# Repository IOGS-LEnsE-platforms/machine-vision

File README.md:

# Machine Vision Platform
Documentation of the pedagogic platform about Machine Vision used during labwors @ LEnsE / IOGS / France

Watch the complete documentation [here !!!](https://iogs-lense.github.io/machine-vision/)

## About Institut d'Optique and LEnsE
The **LEnsE**, ***Laboratoire d'Enseignement Expérimental***, [Website](http://lense.institutoptique.fr/)

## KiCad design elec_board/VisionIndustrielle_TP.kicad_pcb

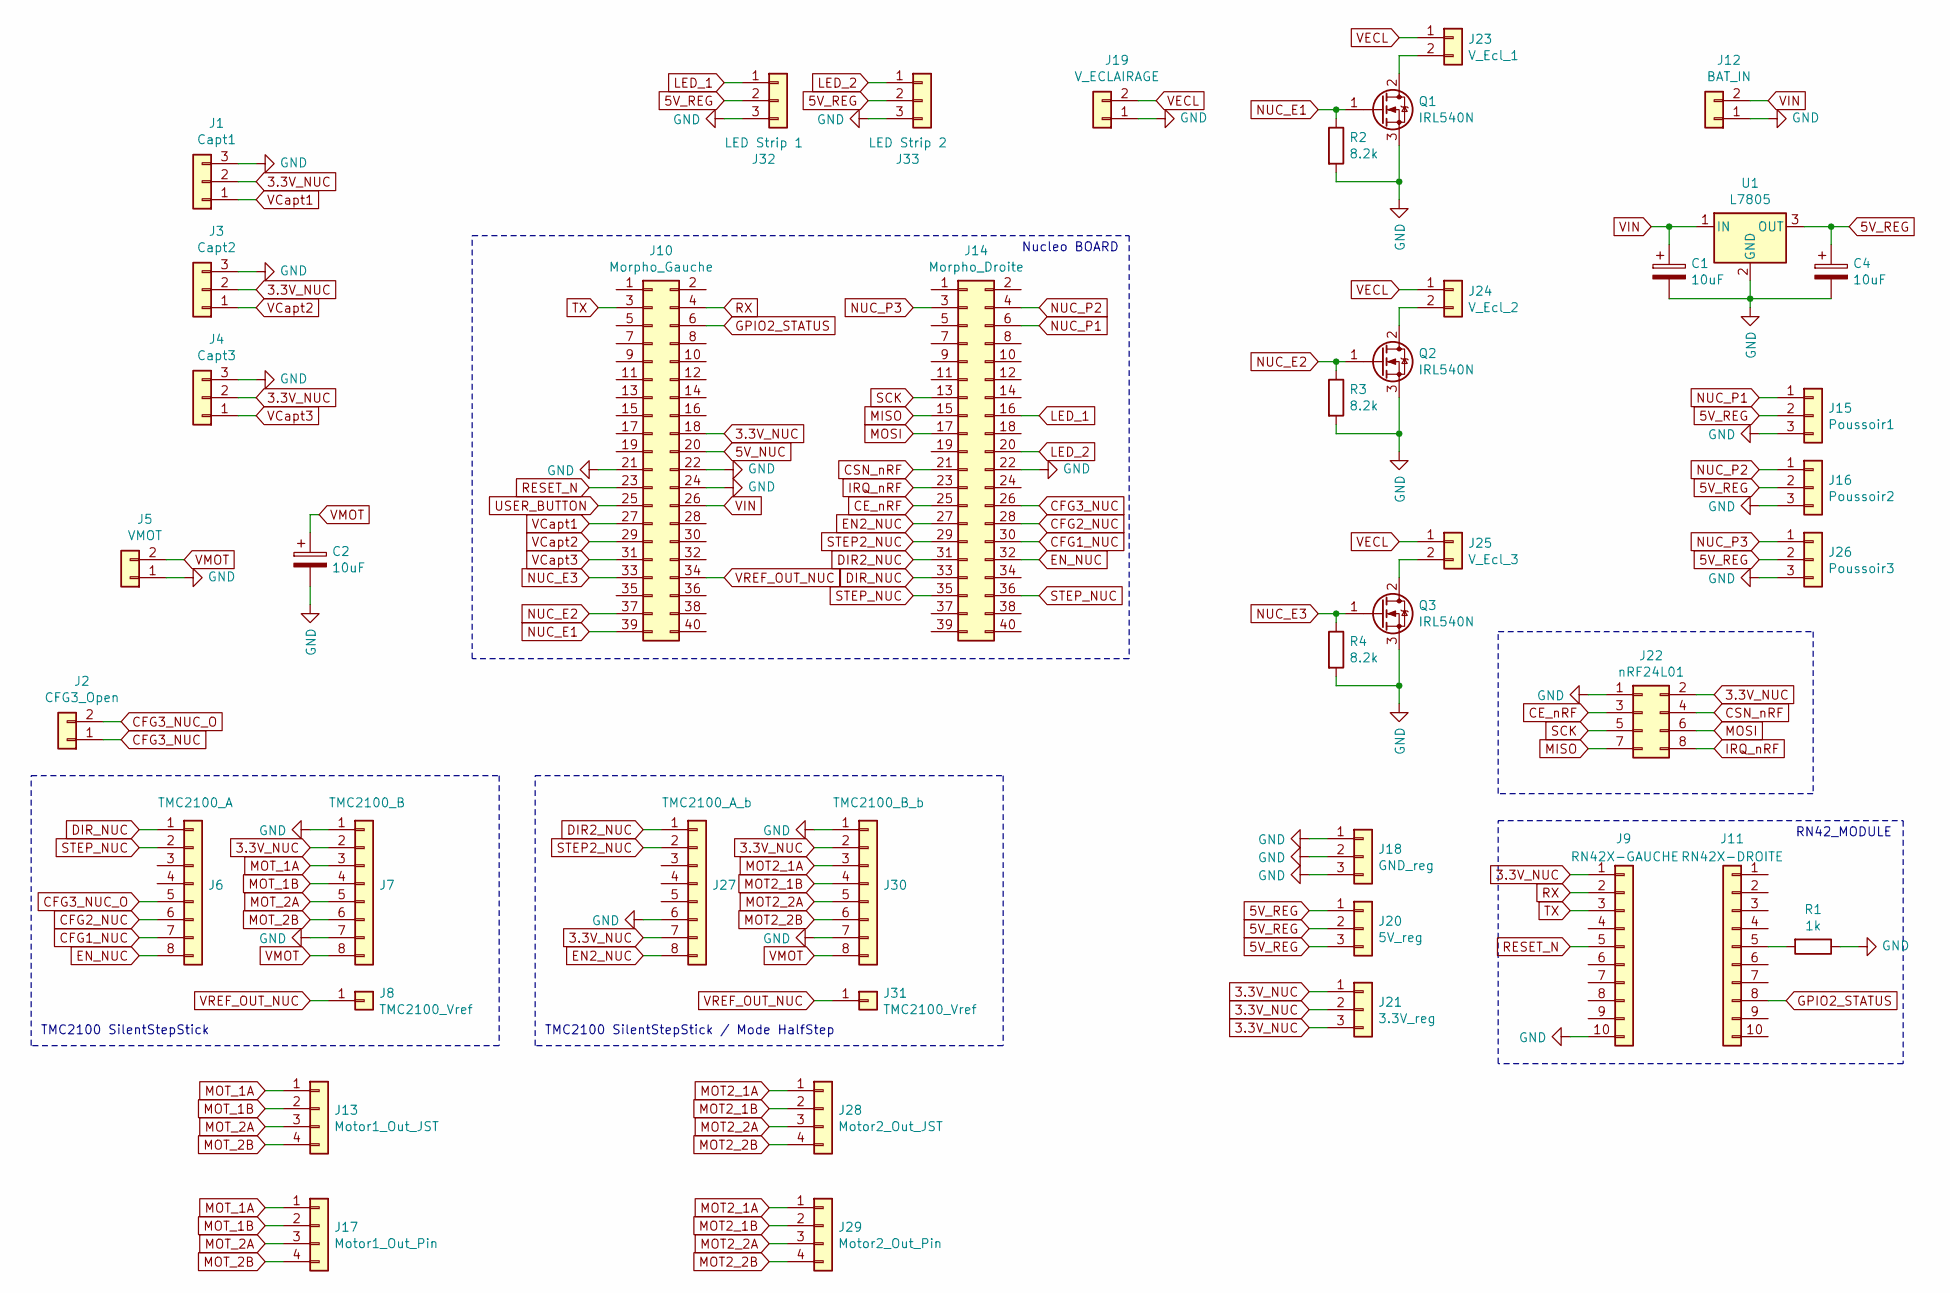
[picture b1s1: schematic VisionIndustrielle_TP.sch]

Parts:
C1, C2, C4: 10uF; CP_Radial_D10.0mm_P5.00mm
J1: Capt1; PinSocket_1x03_P2.54mm_Vertical
J2: CFG3_Open; PinSocket_1x02_P2.54mm_Vertical
J3: Capt2; PinSocket_1x03_P2.54mm_Vertical
J4: Capt3; PinSocket_1x03_P2.54mm_Vertical
J5: VMOT; TerminalBlock_Phoenix_MKDS-3-2-5.08_1x02_P5.08mm_Horizontal
J6: TMC2100_A; PinSocket_1x08_P2.54mm_Vertical
J7: TMC2100_B; PinSocket_1x08_P2.54mm_Vertical
J8, J31: TMC2100_Vref; PinSocket_1x01_P2.54mm_Vertical
J9: RN42X-GAUCHE; PinHeader_1x10_P2.00mm_Vertical
J10: Morpho_Gauche; PinHeader_2x20_P2.54mm_Vertical
J11: RN42X-DROITE; PinHeader_1x10_P2.00mm_Vertical
J12: BAT_IN; TerminalBlock_Phoenix_MKDS-3-2-5.08_1x02_P5.08mm_Horizontal
J13: Motor1_Out_JST; JST_PH_B4B-PH-K_1x04_P2.00mm_Vertical
J14: Morpho_Droite; PinHeader_2x20_P2.54mm_Vertical
J15: Poussoir1; PinHeader_1x03_P2.54mm_Horizontal
J16: Poussoir2; PinHeader_1x03_P2.54mm_Horizontal
J17: Motor1_Out_Pin; PinSocket_1x04_P2.54mm_Vertical
J18: GND_reg; PinHeader_1x03_P2.54mm_Vertical
J19: V_ECLAIRAGE; TerminalBlock_Phoenix_MKDS-3-2-5.08_1x02_P5.08mm_Horizontal
J20: 5V_reg; PinHeader_1x03_P2.54mm_Vertical
J21: 3.3V_reg; PinHeader_1x03_P2.54mm_Vertical
J22: nRF24L01; PinHeader_2x04_P2.54mm_Vertical
J23: V_Ecl_1; TerminalBlock_bornier-2_P5.08mm
J24: V_Ecl_2; TerminalBlock_bornier-2_P5.08mm
J25: V_Ecl_3; TerminalBlock_bornier-2_P5.08mm
J26: Poussoir3; PinHeader_1x03_P2.54mm_Horizontal
J27: TMC2100_A_b; PinSocket_1x08_P2.54mm_Vertical
J28: Motor2_Out_JST; JST_PH_B4B-PH-K_1x04_P2.00mm_Vertical
J29: Motor2_Out_Pin; PinSocket_1x04_P2.54mm_Vertical
J30: TMC2100_B_b; PinSocket_1x08_P2.54mm_Vertical
J32: LED Strip 1; PinSocket_1x03_P2.54mm_Vertical
J33: LED Strip 2; PinSocket_1x03_P2.54mm_Vertical
Q1, Q2, Q3: IRL540N; TO-220-3_Vertical
R1: 1k; R_Axial_DIN0207_L6.3mm_D2.5mm_P10.16mm_Horizontal
R2, R3, R4: 8.2k; R_Axial_DIN0207_L6.3mm_D2.5mm_P10.16mm_Horizontal
U1: L7805; TO-220-3_Horizontal_TabDown

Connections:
3.3V_NUC: J1.2, J3.2, J4.2, J7.2, J9.1, J10.18, J21.1, J21.2, J21.3, J22.2, J27.7, J30.2
5V_NUC: J10.20
5V_REG: C4.1, J15.2, J16.2, J20.1, J20.2, J20.3, J26.2, J32.2, J33.2, U1.3 (OUT)
CE_nRF: J14.25, J22.3
CFG1_NUC: J6.7, J14.30
CFG2_NUC: J6.6, J14.28
CFG3_NUC: J2.1, J14.26
CFG3_NUC_O: J2.2, J6.5
CSN_nRF: J14.21, J22.4
DIR2_NUC: J14.31, J27.1
DIR_NUC: J6.1, J14.33
EN2_NUC: J14.27, J27.8
EN_NUC: J6.8, J14.32
GND: C1.2, C2.2, C4.2, J1.3, J3.3, J4.3, J5.1, J7.1, J7.7, J9.10, J10.21, J10.22, J10.24, J12.1, J14.22, J15.3, J16.3, J18.1, J18.2, J18.3, J19.1, J22.1, J26.3, J27.6, J30.1, J30.7, J32.3, J33.3, Q1.3 (S), Q2.3 (S), Q3.3 (S), R1.1, R2.2, R3.2, R4.2, U1.2 (GND)
GPIO2_STATUS: J10.6, J11.8
IRQ_nRF: J14.23, J22.8
LED_1: J14.16, J32.1
LED_2: J14.20, J33.1
MISO: J14.15, J22.7
MOSI: J14.17, J22.6
MOT2_1A: J28.1, J29.1, J30.3
MOT2_1B: J28.2, J29.2, J30.4
MOT2_2A: J28.3, J29.3, J30.5
MOT2_2B: J28.4, J29.4, J30.6
MOT_1A: J7.3, J13.1, J17.1
MOT_1B: J7.4, J13.2, J17.2
MOT_2A: J7.5, J13.3, J17.3
MOT_2B: J7.6, J13.4, J17.4
NUC_E1: J10.39, Q1.1 (G), R2.1
NUC_E2: J10.37, Q2.1 (G), R3.1
NUC_E3: J10.33, Q3.1 (G), R4.1
NUC_P1: J14.6, J15.1
NUC_P2: J14.4, J16.1
NUC_P3: J14.3, J26.1
unnamed: J11.5, R1.2
unnamed: J23.2, Q1.2 (D)
unnamed: J24.2, Q2.2 (D)
unnamed: J25.2, Q3.2 (D)
RESET_N: J9.5, J10.23
RX: J9.2, J10.4
SCK: J14.13, J22.5
STEP2_NUC: J14.29, J27.2
STEP_NUC: J6.2, J14.35, J14.36
TX: J9.3, J10.3
USER_BUTTON: J10.25
VCapt1: J1.1, J10.27
VCapt2: J3.1, J10.29
VCapt3: J4.1, J10.31
VECL: J19.2, J23.1, J24.1, J25.1
VIN: C1.1, J10.26, J12.2, U1.1 (IN)
VMOT: C2.1, J5.2, J7.8, J30.8
VREF_OUT_NUC: J8.1, J10.34, J31.1

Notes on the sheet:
RN42_MODULE
Nucleo BOARD
TMC2100 SilentStepStick
TMC2100 SilentStepStick / Mode HalfStep

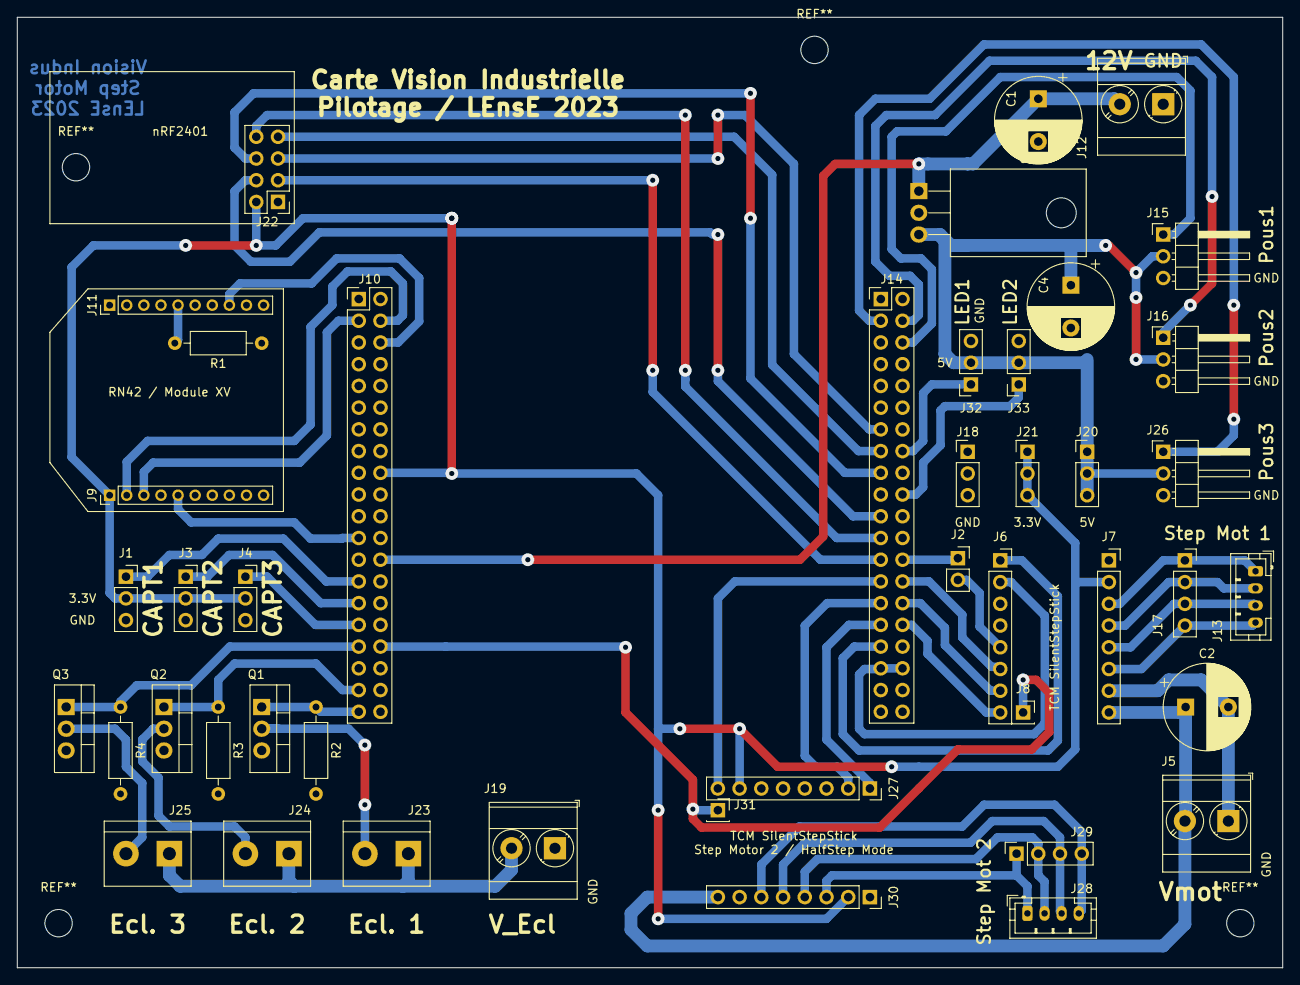
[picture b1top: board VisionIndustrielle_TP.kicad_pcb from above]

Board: 2 copper layers, 148.0 x 111.1 mm, 44 parts (0 on the bottom side), 50 nets.

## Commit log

2024-03-06 First Update - Move from LEnsE organization
2024-03-06 deploy: deb1bb1f00c2fd7c3bcc71b373322e8e230f70bd
2024-03-06 Update Contributors
2024-03-06 deploy: 1782988dc6dbb847983452eb9a7c2e5979842144
2024-03-06 deploy: af77a5fd8c1beb3de072245e93ac906e477f51ae
2024-03-06 deploy: 3be72eaf475cc27e298cd4a95f2e0601247334b3
2024-03-06 deploy: ca31e1b94574a111cb2100438c76607ba2e87e1c
2024-03-06 deploy: e21e0d7082ad8b2f158afa3d3029410a7d24c14a
2024-03-06 deploy: 018843331b4467ff4d55d8699b5ece1de71f92f2
2024-03-06 Update Documentation / Material overview
2024-03-06 deploy: 894b8b5154b2502b9973c56122f9b881b5534531
2024-03-08 deploy: 1901ba623d2323d4eb45a617c672028cd8ee9a91
2024-03-08 Update CSS
2024-03-08 deploy: 8b5d9390be5f0082feca52f3d27435d4d0096db1
2024-03-08 deploy: a7fe34d7fdc356e0ab7256e443ffa75a9448d6c4
2024-03-11 deploy: 487c0d401094ec7c2ff393e5f9b1174e50b6b78a
2024-03-24 deploy: 7a0d2f95227cda03ac5e75acaba1120fbc402f93
2024-04-03 deploy: 0c63b80b288ca174a87c86c4716e08edd4908fab
2024-04-03 deploy: e5d5c2dc80ec76be55f5df0b240a4cd9820cf303
2024-04-03 deploy: fa6d5454141928e599569ea2a1299a85ed1d75b1
2024-05-06 Adding PIMS 2022 program
2024-05-06 deploy: a5b9ea5b80e21e4ee1498eedb4d9e651d8b34d55
2024-05-06 Update Poster
2025-02-21 deploy: d2573f46a9c1166a31d20e6a213874a149288363
2025-05-11 deploy: 84e57b8c33155aa42b8a6b7e41b12e4e6503e587
